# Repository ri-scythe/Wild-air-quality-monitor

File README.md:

# wild-air-quality-monitor
An air quality monitor I've decided to make because of how bad the air in my city can be sometimes. It has CO2, humidity and temperature, PM sensors.

# CAD
Made in Fusion360.

# PCB
Made in KiCad.

Schematic:

PCB:

# BOM

- [Arduino Pro Mini 5V](https://aliexpress.ru/item/1005009411579511.html?shpMethod=AE_CN_SUPER_ECONOMY_G&sku_id=12000049016718294&spm=a2g2w.productlist.search_results.0.6b4b46cfdHwfpU)
- [PMS5003](https://aliexpress.ru/item/1005009157717878.html?shpMethod=CAINIAO_STANDARD&sku_id=12000048130179862&spm=a2g2w.productlist.search_results.2.38b27b89OJPgvz)
- [DHT22](https://aliexpress.ru/item/1005010283810231.html?shpMethod=CAINIAO_STANDARD&sku_id=12000051781867490&spm=a2g2w.productlist.search_results.3.27904037HZJH4O)
- [MHZ19B](https://aliexpress.ru/item/32651094869.html?shpMethod=CAINIAO_STANDARD&sku_id=59748440079&spm=a2g2w.productlist.search_results.7.12313c563kKEUA)
- [DS3231 RTC](https://aliexpress.ru/item/1005009372357241.html?shpMethod=AE_CN_SUPER_ECONOMY_G&sku_id=12000048902048959&spm=a2g2w.productlist.search_results.2.6ac55c513ZLA3G)
- [Nextion 2.8" Display](https://aliexpress.ru/item/4001240732911.html?sku_id=12000016667327153&spm=a2g2w.productlist.search_results.1.33e64887Og5KYc)
- [2x EG1218 switch](https://aliexpress.ru/item/1005010262255606.html?shpMethod=AE_CN_SUPER_ECONOMY_G&sku_id=12000051707116759&spm=a2g2w.productlist.search_results.1.504416efuBK6pg)
- [Mini USB Connector](https://aliexpress.ru/item/1005008106928890.html?shpMethod=CAINIAO_SUPER_ECONOMY&sku_id=12000043796686582&spm=a2g2w.productlist.search_results.0.5fce5845O0T4ku)
- [6x M3 MF 10mm spacers](https://aliexpress.ru/item/1005007389190533.html?shpMethod=CAINIAO_SUPER_ECONOMY&sku_id=12000040550999733&spm=a2g2w.productlist.search_results.0.15aa3e369qvhKq)
- [6x M3 FF 30mm spacers](https://aliexpress.ru/item/1005004127890102.html?sku_id=12000029443156235&spm=a2g2w.productlist.search_results.1.15aa3e369qvhKq)
- [12x M3 screws](https://aliexpress.ru/item/4001199728978.html?sku_id=10000015289904605&spm=a2g2w.productlist.search_results.0.76054df3SX27yN)
- [FTDI USB TTL]()

# Details:

I've used this tutorial as a reference: https://howtomechatronics.com/projects/diy-air-quality-monitor-pm2-5-co2-voc-ozone-temp-hum-arduino-meter/

I also used Claude AI to make the firmware for Arduino.

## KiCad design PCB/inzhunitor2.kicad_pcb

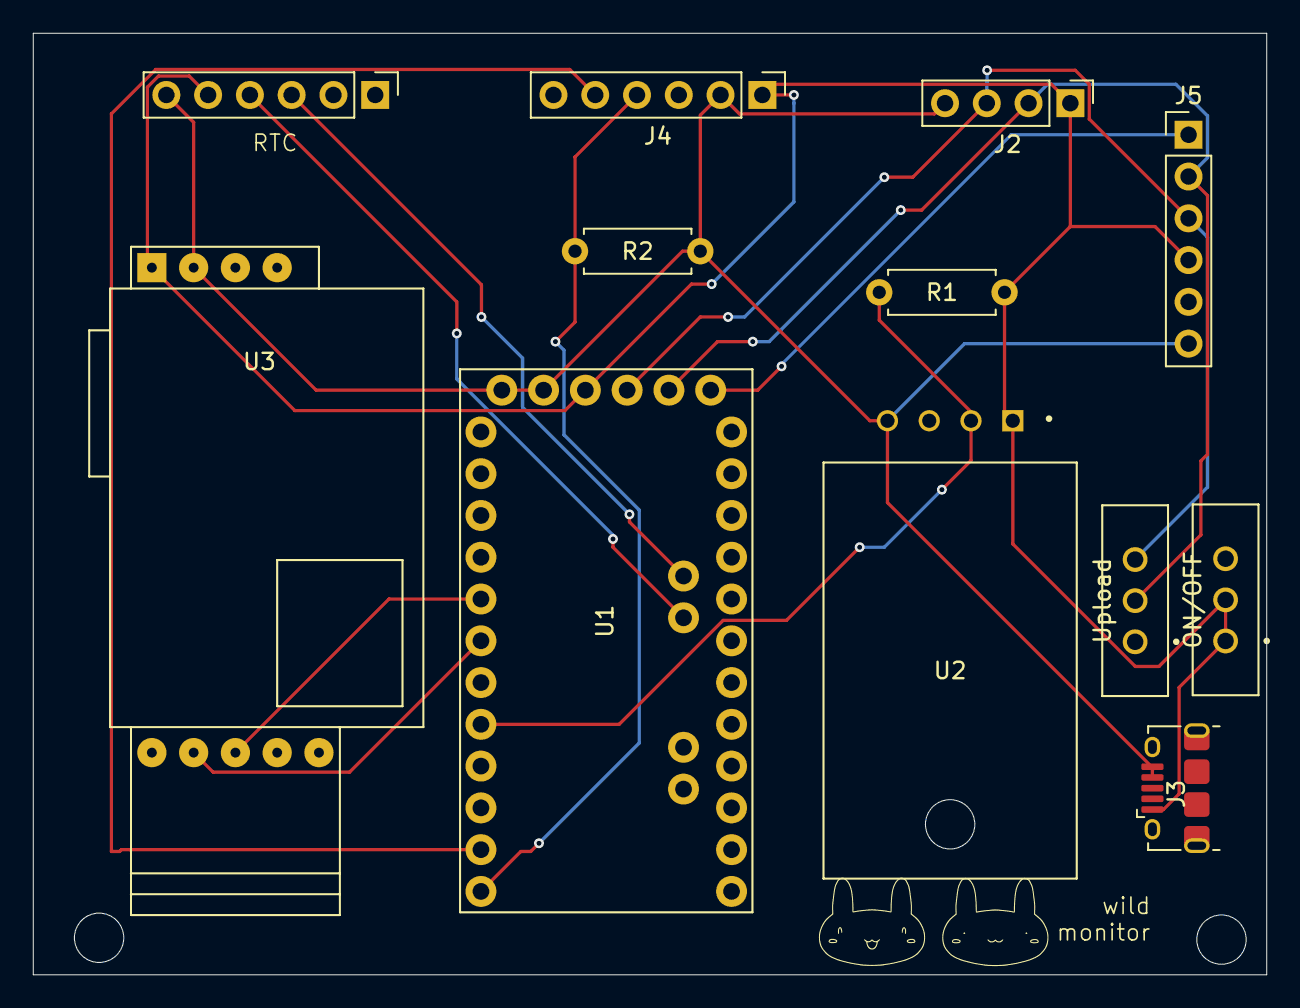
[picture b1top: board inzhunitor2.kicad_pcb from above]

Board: 2 copper layers, 75.0 x 57.2 mm, 12 parts (0 on the bottom side), 12 nets.

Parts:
J1: DS3231 RTC; PinHeader_1x06_P2.54mm_Vertical
J2: Display; PinHeader_1x04_P2.54mm_Vertical
J3: 10118194-0001LF; USB_Micro-B_Amphenol_10118194-0001LF_Horizontal
J4: PMS5003; PinHeader_1x06_P2.54mm_Vertical
J5: FTDI USB-TTL; PinHeader_1x06_P2.54mm_Vertical
ON/OFF: EG1218 ON/OFF; SW_EG1218
R1: 10K; R_Axial_DIN0207_L6.3mm_D2.5mm_P7.62mm_Horizontal
R2: 1K; R_Axial_DIN0207_L6.3mm_D2.5mm_P7.62mm_Horizontal
U1: ARDUINO_PRO_MINI 5V; MODULE_ARDUINO_PRO_MINI
U2: DHT22; XDCR_DHT22
U3: MH-Z19B
Upload: EG1218 Upload; SW_EG1218

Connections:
+5V: J1.5, J2.1, J3.1 (VCC), J4.1, J5.4, ON/OFF.1, ON/OFF.2, R1.1, U1.JP1_4 (VCC), U2.1 (VDD), U3.VIN
GND: J1.6, J2.4, J3.4 (ID), J3.5 (GND), J4.2, J5.6, R2.2, U1.JP1_5 (GND), U1.JP1_6 (GND), U2.4 (GND), U3.GND
unnamed: J1.3, U1.JP2_2 (A5)
unnamed: J1.4, U1.JP2_1 (A4)
unnamed: J2.2, J5.2, U1.JP1_2 (TXO), Upload.2
unnamed: J2.3, J5.3, U1.JP1_3 (RXI), Upload.3
unnamed: J4.4, R2.1, U1.JP7_1 (D9)
unnamed: J4.5, U1.JP7_2 (D8)
unnamed: J5.1, U1.JP1_1 (DTR)
unnamed: U1.JP7_8 (D2), U3.TX
unnamed: U1.JP7_7 (D3), U3.RX
unnamed: R1.2, U1.JP7_5 (D5), U2.2 (DATA)

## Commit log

2026-03-23 Create a
2026-03-23 Create s
2026-03-23 Update README with project details and images
    Added project description, CAD, and PCB details with images.
2026-03-23 Add CAD section to README
    Added a section about CAD design in Fusion360.
2026-03-23 Update project title to lowercase
2026-03-23 Create aaa
2026-03-23 Include details and tutorial reference in README
    Added a reference tutorial for the project.
2026-03-24 Fix header formatting for PCB section in README
2026-03-25 Add mention of Claude AI in README
2026-03-25 Create Aa
2026-03-25 Update README to include Claude AI reference
    Added mention of using Claude AI for Arduino firmware.
2026-03-25 Enhance BOM with new components and links
    Updated BOM section with additional components and links.
2026-03-25 Update spacer and screw listings in README
    Removed unnecessary spacer items and added new spacer and screw links.
2026-03-25 Fix formatting of spacer and screw links in README
2026-03-25 Update BOM items with correct component names
2026-03-25 Update BOM with product links
2026-03-25 Update link for M2.5 and M3 screws
2026-03-25 Update README with total cost information
    Added total cost in KZT and USD to the README.
2026-03-25 Revise project description in README
    Updated project description to include sensor details.
2026-04-07 Modify BOM with new component and update links
    Updated the list of components in the BOM and added a new item.
